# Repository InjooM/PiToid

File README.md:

# PiToid

## Intro
Small beginner's electronics project with Raspberry Pi Zero

This is a small project I started about mid-way through my first semester as a freshman at the University of Georgia. It is a Raspberry Pi in an Altoids Tin that acts as an emulator for video games through Retropie. In order to have a functioning "gameboy" I needed several components:

- A display
- An audio system
- A power management system
- Controls

## Display
For the display, I am using a 1.8" TFT display sold from Adafruit that came with a display driver. It uses SPI to communicate with the Raspberry Pi, so I designed a compact breakout board, referenced from the Adafruit breakout board, that fit my Altoids tin and used an FPC connector.

## Audio
For audio, I configured some of the GPIO pins of the RPi to output audio through PWM, ran it though a low-pass filter, then into an LM4810 audio amp with a 2-gang potentiometer acting as the feedback resistors for the amp. The output is a switching 3.5mm audio jack that runs into 2 8 Ohm speakers. This way I can plug in headphones as well.

## Power
For power management I am using a 3.7V Li-Poly battery sold by Adafruit, and I designed a battery charger and step-up, referenced from the Adafruit PowerBoost 1000 Charger. It also has load-sharing capabilites so when plugged in, the battery will only be charging.

## Controls
For controls I designed a breakout board for the Raspberry Pi and soldered tactile switches onto it, which are connected to the GPIO pins. The Pi is running Adafruit's Retrogame, which configures some GPIO pins as keyboard inputs.

## Final Words
The purpose of this project was not simply to build a DIY gameboy, although I do find gameboys to be fun. I mainly wanted to do this project because I wanted more hands-on experience designing and manufacturing PCB's, as well as putting my circuit analysis skills to the test. Reverse engineering the schematics from Adafruit and reading the datasheets for all the complicated components was difficult, however I believe it helped greatly in developing my electronics design skills. I plan on using these skills in the future for other applications, such as specific instrumentation design.

Most, if not all, of my boards are designed through EAGLE, and fabricated through OshPark. I ordered all my components from Digi-key or Mouser.

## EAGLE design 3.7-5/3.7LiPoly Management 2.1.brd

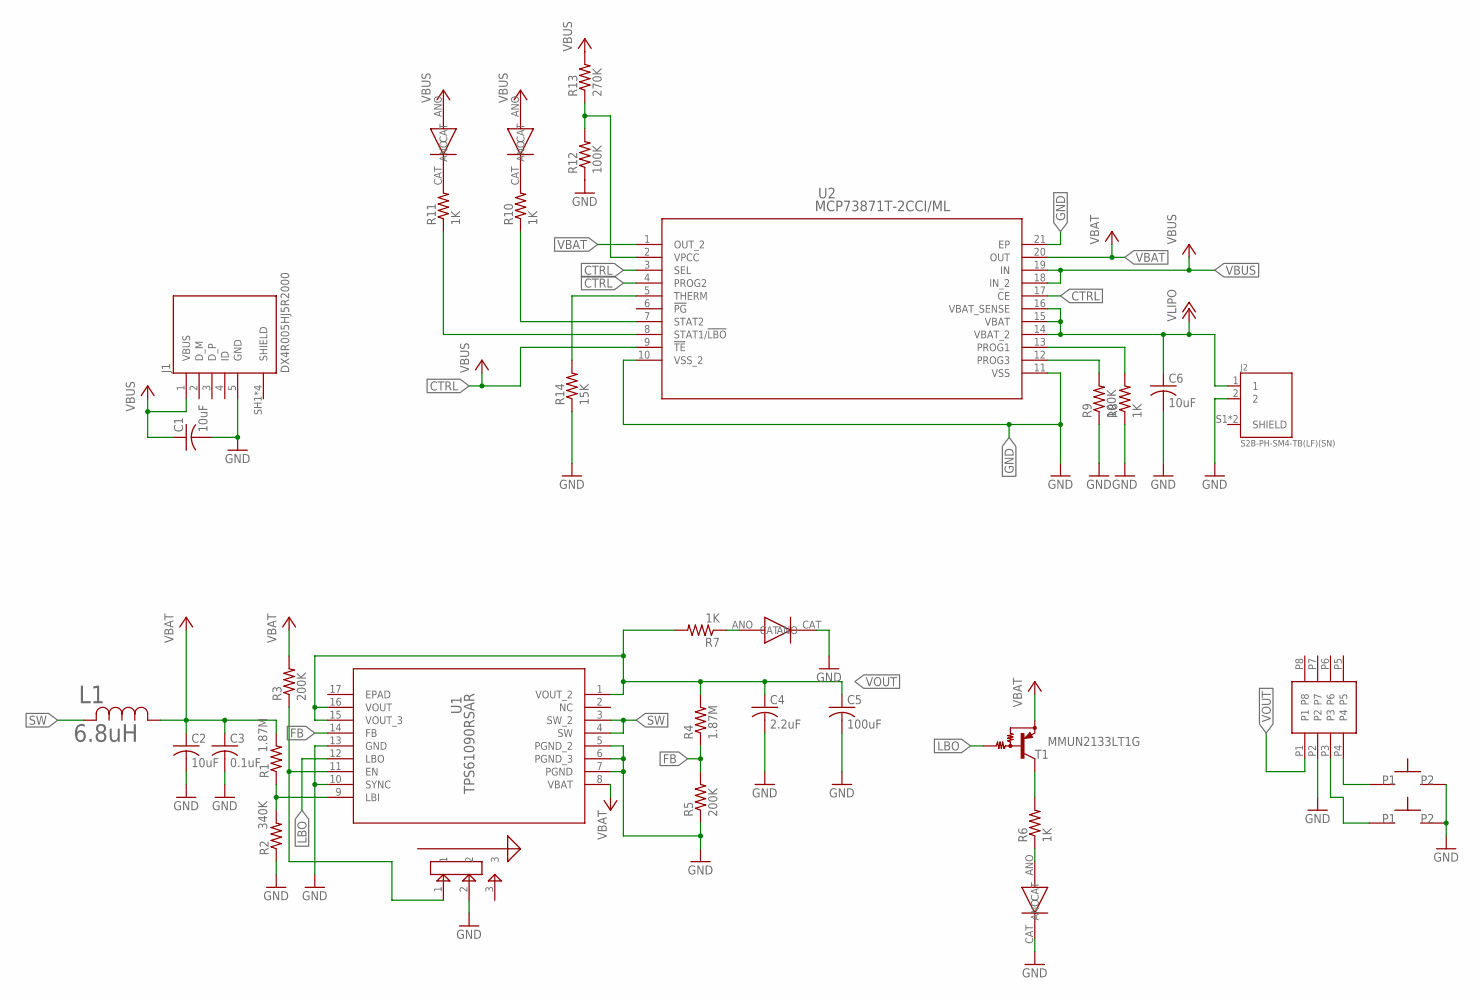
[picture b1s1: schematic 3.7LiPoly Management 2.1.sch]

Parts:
C1, C2, C6: 10uF; C0805
C3: 0.1uF; C0805
C4: 2.2uF; C0805
C5: 100uF; C0805
CHARGE: YELLOW; WP934AD
DONE: GREEN; WP934AD
H1: M22-6340442
J1: DX4R005HJ5R2000; JAE_DX4R005HJ5R2000
J2: S2B-PH-SM4-TB(LF)(SN); JST_S2B-PH-SM4-TB(LF)(SN)
L1: 6.8uH; IND_5028
LBO: RED; WP934AD
POWERON: BLUE; WP934EW
R1, R4: 1.87M; R0805
R2: 340K; R0805
R3, R5: 200K; R0805
R6, R7, R8, R10, R11: 1K; R0805
R9, R12: 100K; R0805
R13: 270K; R0805
R14: 15K; R0805
T1: MMUN2133LT1G; SC59-BEC
U1: TPS61090RSAR; RSA16_2P7X2P7
U2: MCP73871T-2CCI/ML; QFN20_4X4MC
U$1, U$3: SPST_TACTILE_SWITCHRIGHTANGLEBENT; SPST_TACTILESWITCH_TL3360CF185Q_BENTFRAME
U$2: JS102011SAQN

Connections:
+3V3: CHARGE.ANO, DONE.ANO, R13.2
CTRL: U2.3 (SEL), U2.4 (PROG2), U2.9 (!TE), U2.17 (CE)
FB: R4.1, R5.2, U1.14 (FB)
GND: C1.2, C2.2, C3.2, C4.2, C5.2, C6.2, H1.P2, J1.5 (GND), J2.2, LBO.CAT, POWERON.CAT, R2.1, R5.1, R8.1, R9.1, R12.1, R14.1, U1.5 (PGND_2), U1.6 (PGND_3), U1.7 (PGND), U1.10 (SYNC), U1.13 (GND), U2.10 (VSS_2), U2.11 (VSS), U2.21 (EP), U$1.P$2, U$2.2, U$3.P$2
LBO: T1.B, U1.12 (LBO)
unnamed: R1.1, R2.2, U1.9 (LBI)
unnamed: R3.1, U1.11 (EN), U$2.1
unnamed: CHARGE.CAT, R11.2
unnamed: R8.2, U2.13 (PROG1)
unnamed: R6.2, T1.C
unnamed: LBO.ANO, R6.1
unnamed: POWERON.ANO, R7.1
unnamed: R9.2, U2.12 (PROG3)
unnamed: DONE.CAT, R10.2
unnamed: H1.P4, U$3.P$1
unnamed: R11.1, U2.8 (STAT1/!LBO)
unnamed: R10.1, U2.7 (STAT2)
unnamed: R14.2, U2.5 (THERM)
unnamed: R12.2, R13.1, U2.2 (VPCC)
unnamed: H1.P3, U$1.P$1
SW: L1.2, U1.3 (SW_2), U1.4 (SW)
VBAT: C2.1, C3.1, L1.1, R1.2, R3.2, T1.E, U1.8 (VBAT), U2.1 (OUT_2), U2.20 (OUT)
VBUS: C1.1, J1.1 (VBUS), U2.18 (IN_2), U2.19 (IN)
VLIPO: C6.1, J2.1, U2.14 (VBAT_2), U2.15 (VBAT), U2.16 (VBAT_SENSE)
VOUT: C4.1, C5.1, H1.P1, R4.2, R7.2, U1.1 (VOUT_2), U1.15 (VOUT_3), U1.16 (VOUT)

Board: 2 copper layers, 34 parts (0 on the bottom side), 25 nets, no tracks yet.

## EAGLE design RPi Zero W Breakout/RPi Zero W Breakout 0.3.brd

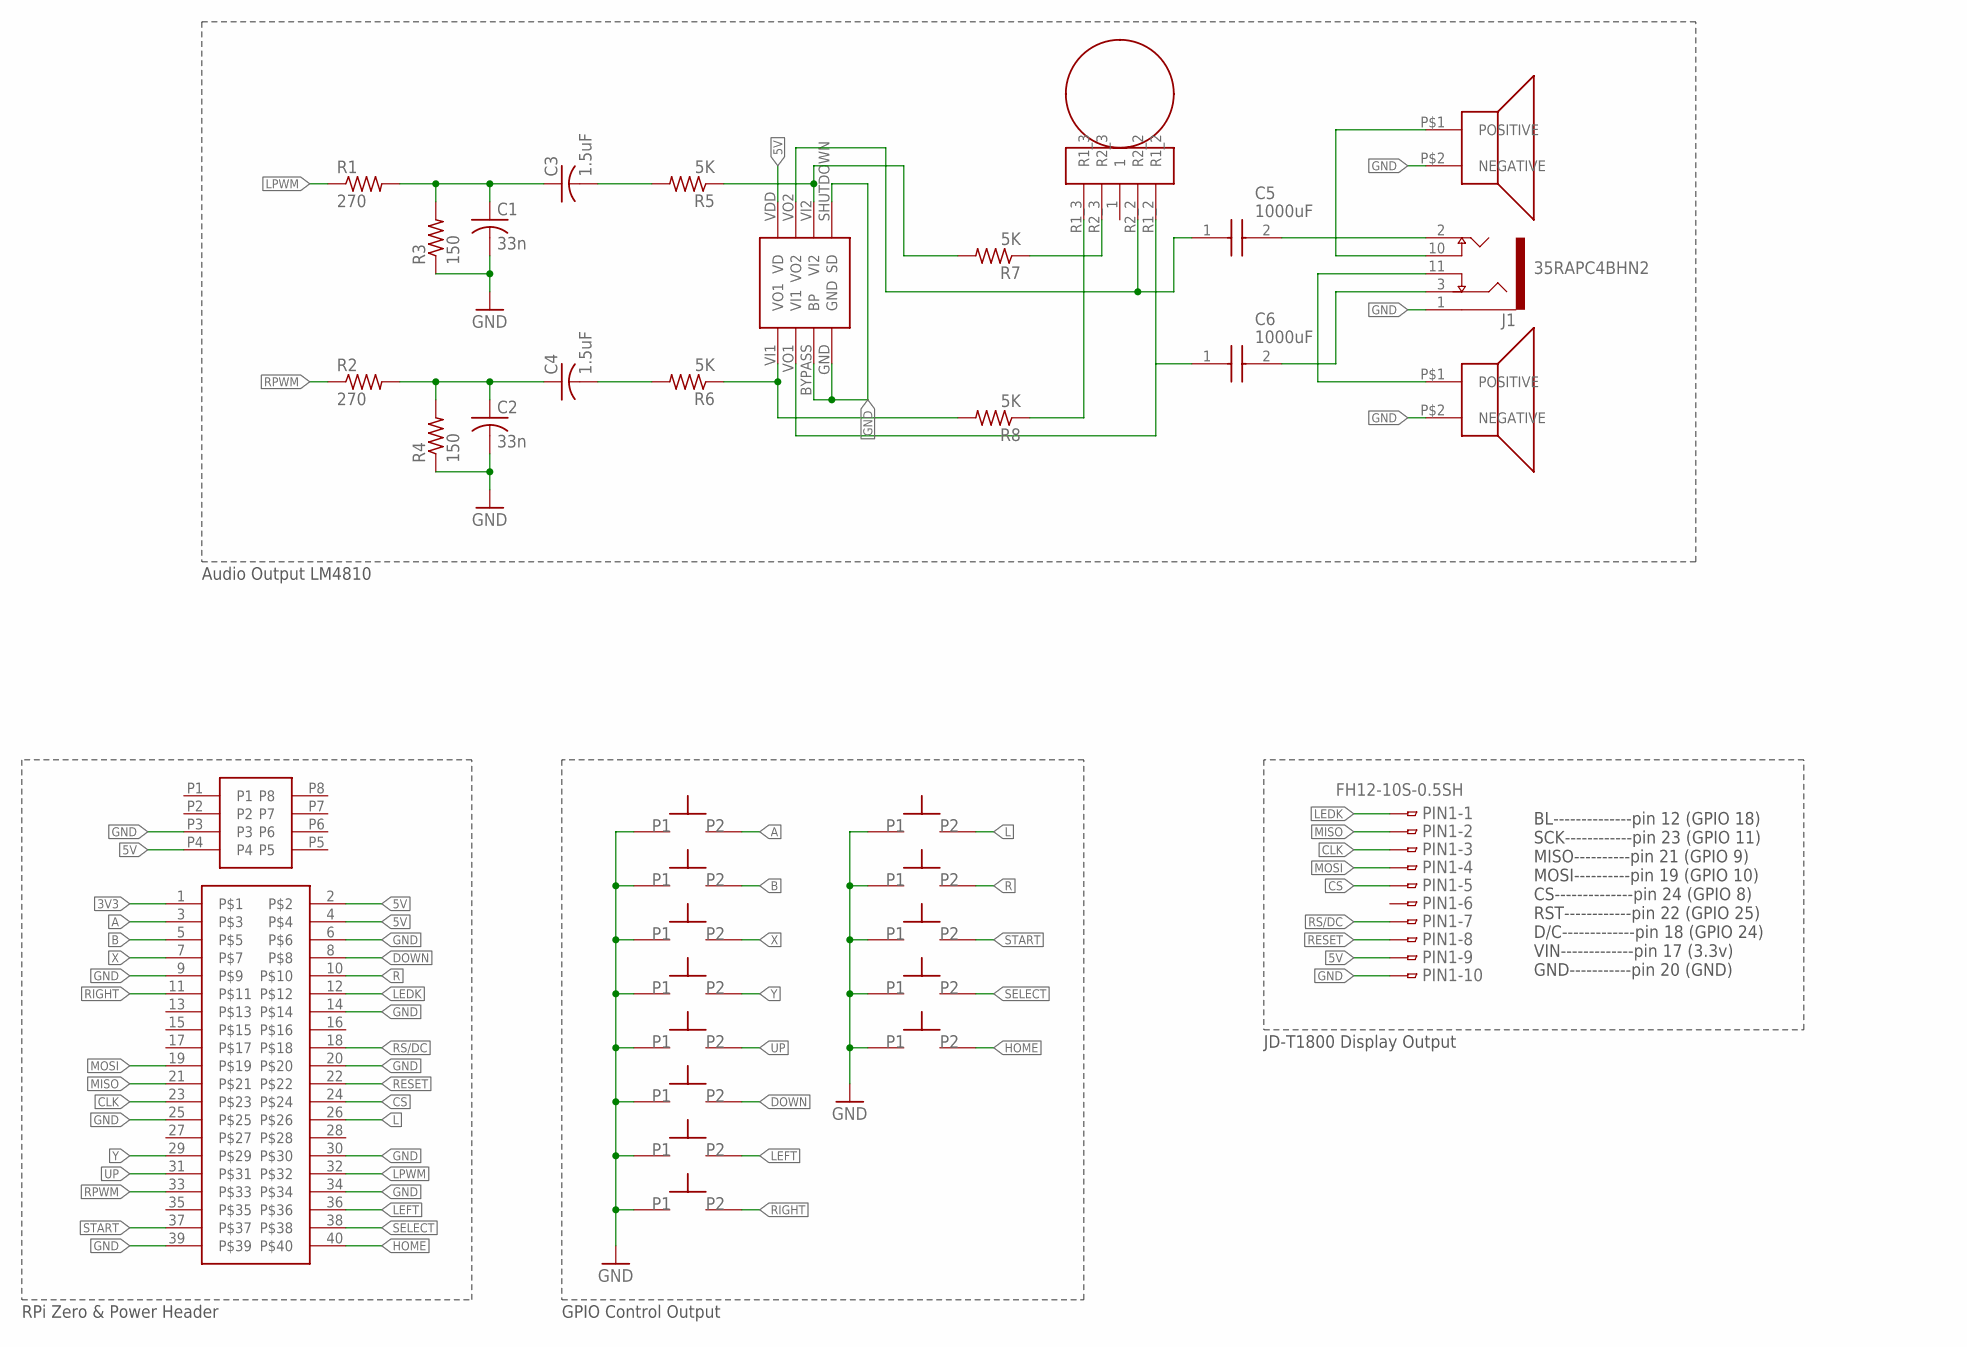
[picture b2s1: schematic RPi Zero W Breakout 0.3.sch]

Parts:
A: SPST_TACTILE_SWITCH; SPST_TACTILESWITCH_TL3301PF160QG
B: SPST_TACTILESWITCH_TL3301PF160QG
C1, C2: 33n; C0805K
C3, C4: 1.5uF; C0805K
C5, C6: 1000uF; UWT(8X10)
DOWN: SPST_TACTILESWITCH_TL3301PF160QG
HOME: SPST_TACTILESWITCH_TL3301PF160QG
J1: 35RAPC4BHN2; SWITCHCRAFT_35RAPC4BHN2
LEFT: SPST_TACTILESWITCH_TL3301PF160QG
LSPK: SP-1208
PIN1: FH12-10S-0.5SH
R1, R2: 270; R0805
R3, R4: 150; R0805
R5, R6, R7, R8: 5K; R0805
RF: RK14J12A0A0K
RIGHT: SPST_TACTILESWITCH_TL3301PF160QG
RSPK: SP-1208
SELECT: SPST_TACTILESWITCH_TL3301PF160QG
START: SPST_TACTILE_SWITCH; SPST_TACTILESWITCH_TL3301PF160QG
U$1: RPI_ZERO
U$2: LM4810MM/NOPBCT-ND; NOPBCT-ND
U$3: M22-6340442
U$4, U$5: SPST_TACTILE_SWITCHRIGHTANGLEBENT; SPST_TACTILESWITCH_TL3360CF185Q_BENTFRAME
UP: SPST_TACTILESWITCH_TL3301PF160QG
X: SPST_TACTILESWITCH_TL3301PF160QG
Y: SPST_TACTILESWITCH_TL3301PF160QG

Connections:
3V3: U$1.1
5V: PIN1.9, U$1.2, U$1.4, U$2.VDD (VD), U$3.P4
A: A.P$3, U$1.3
B: B.P$3, U$1.5
CLK: PIN1.3, U$1.23
CS: PIN1.5, U$1.24
DOWN: DOWN.P$3, U$1.8
GND: A.P$1, B.P$1, C1.2, C2.2, DOWN.P$1, HOME.P$1, J1.1, LEFT.P$1, LSPK.P$2 (NEGATIVE), PIN1.10, R3.1, R4.1, RIGHT.P$1, RSPK.P$2 (NEGATIVE), SELECT.P$1, START.P$1, U$1.6, U$1.9, U$1.14, U$1.20, U$1.25, U$1.30, U$1.34, U$1.39, U$2.BYPASS (BP), U$2.GND, U$2.SHUTDOWN (SD), U$3.P3, U$4.P$1, U$5.P$1, UP.P$1, X.P$1, Y.P$1
HOME: HOME.P$3, U$1.40
L: U$1.26, U$4.P$2
LEDK: PIN1.1, U$1.12
LEFT: LEFT.P$3, U$1.36
LPWM: R1.1, U$1.32
MISO: PIN1.2, U$1.21
MOSI: PIN1.4, U$1.19
unnamed: C1.1, C3.1, R1.2, R3.2
unnamed: C2.1, C4.1, R2.2, R4.2
unnamed: C3.2, R5.2
unnamed: R7.1, RF.R2_3
unnamed: C4.2, R6.2
unnamed: R8.1, RF.R1_3
unnamed: C6.1 (+), RF.R1_2, U$2.VO1 (VI1)
unnamed: C5.1 (+), RF.R2_2, U$2.VO2
unnamed: C5.2 (-), J1.2
unnamed: C6.2 (-), J1.3
unnamed: J1.10, LSPK.P$1 (POSITIVE)
unnamed: J1.11, RSPK.P$1 (POSITIVE)
unnamed: R5.1, R7.2, U$2.VI2
unnamed: R6.1, R8.2, U$2.VI1 (VO1)
R: U$1.10, U$5.P$2
RESET: PIN1.8, U$1.22
RIGHT: RIGHT.P$3, U$1.11
RPWM: R2.1, U$1.33
RS/DC: PIN1.7, U$1.18
SELECT: SELECT.P$3, U$1.38
START: START.P$3, U$1.37
UP: U$1.31, UP.P$3
X: U$1.7, X.P$3
Y: U$1.29, Y.P$3

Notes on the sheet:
BL--------------pin 12 (GPIO 18) SCK------------pin 23 (GPIO 11) MISO----------pin 21 (GPIO 9) MOSI----------pin 19 (GPIO 10) CS--------------pin 24 (GPIO 8) RST------------pin 22 (GPIO 25) D/C-------------pin 18 (GPIO 24) VIN-------------pin 17 (3.3v) GND-----------pin 20 (GND)
RPi Zero & Power Header
GPIO Control Output
JD-T1800 Display Output
Audio Output LM4810

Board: 2 copper layers, 35 parts (4 on the bottom side), 38 nets, no tracks yet.

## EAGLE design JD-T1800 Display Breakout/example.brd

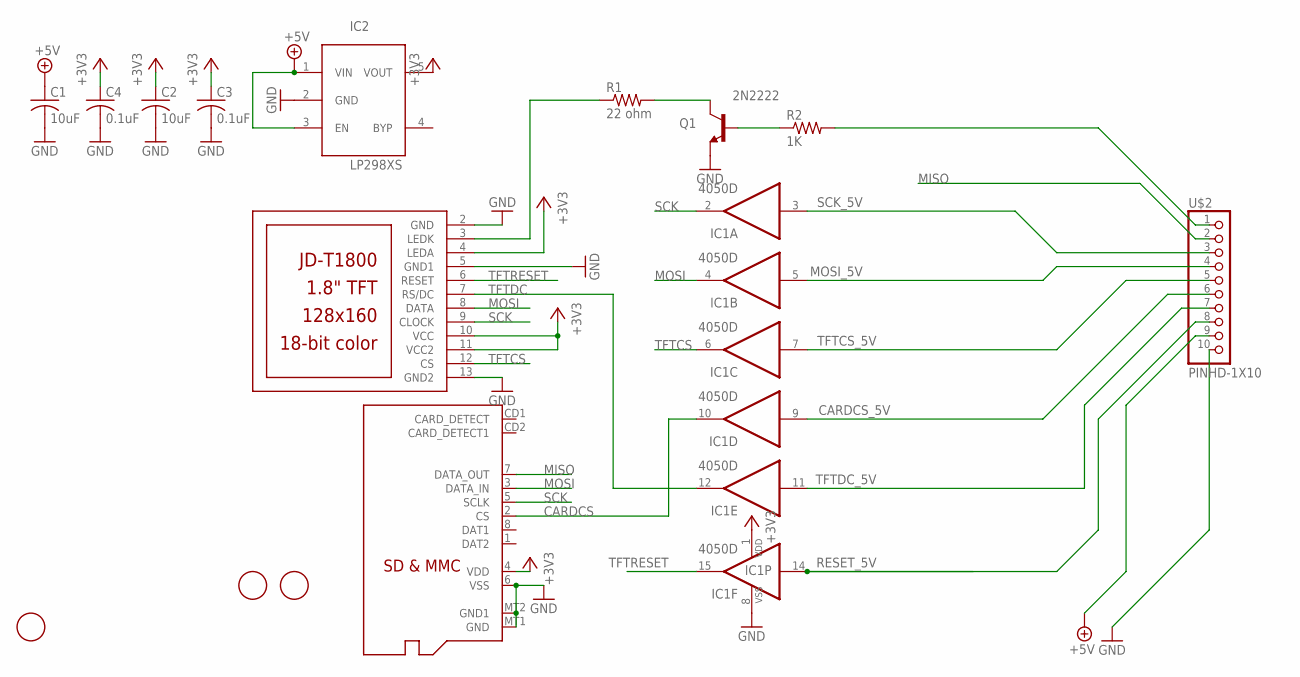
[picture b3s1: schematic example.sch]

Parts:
C1, C2: 10uF; C0805K
C3, C4: 0.1uF; C0805K
IC1: 4050D; SO16
IC2: LP298XS; SOT23-5L
Q1: 2N2222; SOT23-BEC
Q2: MICROSD
R1: 22 ohm; R0805
R2: 1K; R0805
U$1: JD-T1800
U$2: PINHD-1X10; 1X10-BIG
U$3, U$4, U$5: FIDUCIAL; FIDUCIAL_1MM

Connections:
+3V3: C2.1, C3.1, C4.1, IC1.1 (VDD), IC2.5 (VOUT), Q2.4 (VDD), U$1.4 (LEDA), U$1.10 (VCC), U$1.11 (VCC2)
+5V: C1.1, IC2.1 (VIN), IC2.3 (EN), U$2.9
CARDCS: IC1.10 (O), Q2.2 (CS)
CARDCS_5V: IC1.9 (I), U$2.6
GND: C1.2, C2.2, C3.2, C4.2, IC1.8 (VSS), IC2.2 (GND), Q1.E, Q2.6 (VSS), Q2.MT1 (GND), Q2.MT2 (GND1), U$1.2 (GND), U$1.5 (GND1), U$1.13 (GND2), U$2.10
MISO: Q2.7 (DATA_OUT), U$2.2
MOSI: IC1.4 (O), Q2.3 (DATA_IN), U$1.8 (DATA)
MOSI_5V: IC1.5 (I), U$2.4
unnamed: Q1.B, R2.1
unnamed: R1.1, U$1.3 (LEDK)
unnamed: Q1.C, R1.2
unnamed: R2.2, U$2.1
RESET_5V: IC1.14 (I), U$2.8
SCK: IC1.2 (O), Q2.5 (SCLK), U$1.9 (CLOCK)
SCK_5V: IC1.3 (I), U$2.3
TFTCS: IC1.6 (O), U$1.12 (CS)
TFTCS_5V: IC1.7 (I), U$2.5
TFTDC: IC1.12 (O), U$1.7 (RS/DC)
TFTDC_5V: IC1.11 (I), U$2.7
TFTRESET: IC1.15 (O), U$1.6 (RESET)

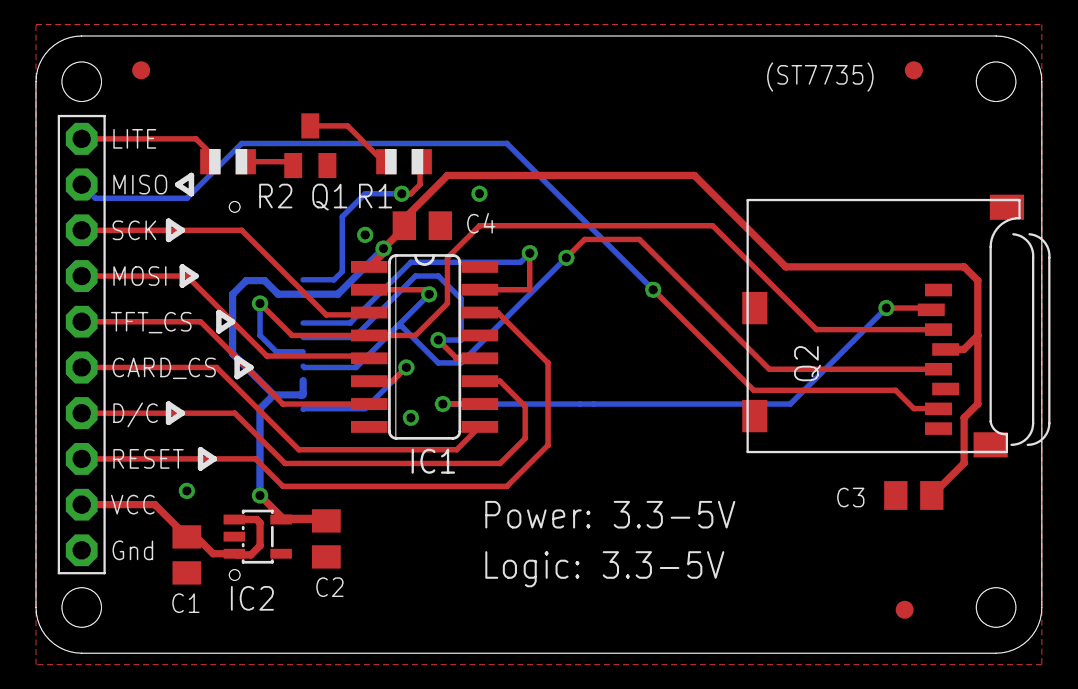
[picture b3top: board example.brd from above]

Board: 2 copper layers, 55.9 x 34.3 mm, 15 parts (1 on the bottom side), 20 nets.

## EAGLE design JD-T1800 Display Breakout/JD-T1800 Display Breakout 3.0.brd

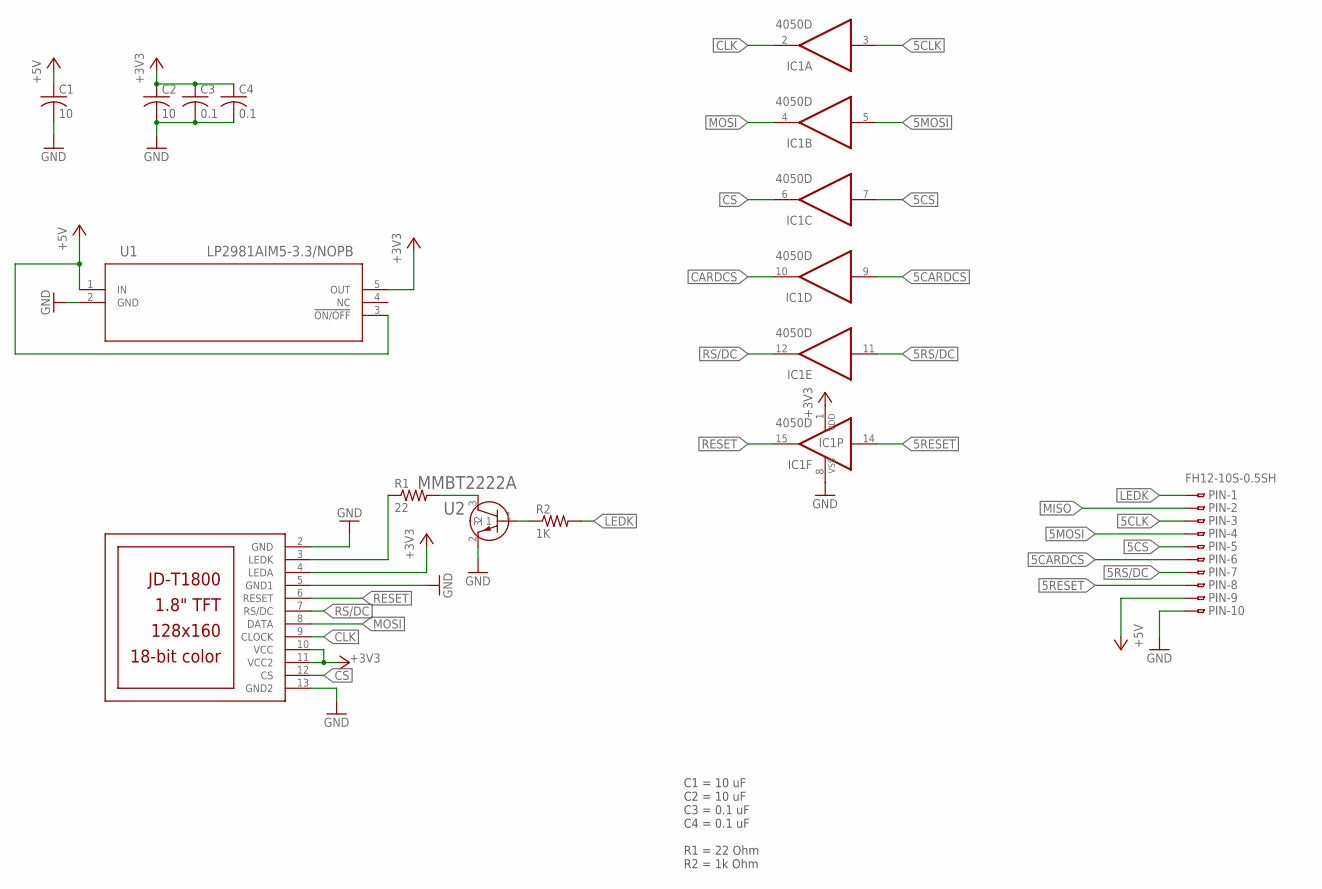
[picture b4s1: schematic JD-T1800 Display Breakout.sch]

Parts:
C1, C2: 10; C0805
C3, C4: 0.1; C0805
IC1: 4050D; SO16
PIN: FH12-10S-0.5SH
R1: 22; R0805
R2: 1K; R0805
U1: LP2981AIM5-3.3/NOPB; MF05A
U2: MMBT2222A; SOT23
U$1: JD-T1800

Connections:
5CARDCS: IC1.9 (I), PIN.6
5CLK: IC1.3 (I), PIN.3
5CS: IC1.7 (I), PIN.5
5MOSI: IC1.5 (I), PIN.4
5RESET: IC1.14 (I), PIN.8
5RS/DC: IC1.11 (I), PIN.7
+3V3: C2.1, C3.1, C4.1, IC1.1 (VDD), U1.5 (OUT), U$1.4 (LEDA), U$1.10 (VCC), U$1.11 (VCC2)
+5V: C1.1, PIN.9, U1.1 (IN), U1.3 (!ON/OFF)
CARDCS: IC1.10 (O)
CLK: IC1.2 (O), U$1.9 (CLOCK)
CS: IC1.6 (O), U$1.12 (CS)
GND: C1.2, C2.2, C3.2, C4.2, IC1.8 (VSS), PIN.10, U1.2 (GND), U2.2, U$1.2 (GND), U$1.5 (GND1), U$1.13 (GND2)
LEDK: PIN.1, R2.2
MISO: PIN.2
MOSI: IC1.4 (O), U$1.8 (DATA)
unnamed: R1.1, U$1.3 (LEDK)
unnamed: R1.2, U2.3
unnamed: R2.1, U2.1
RESET: IC1.15 (O), U$1.6 (RESET)
RS/DC: IC1.12 (O), U$1.7 (RS/DC)

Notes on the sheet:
C1 = 10 uF C2 = 10 uF C3 = 0.1 uF C4 = 0.1 uF R1 = 22 Ohm R2 = 1k Ohm

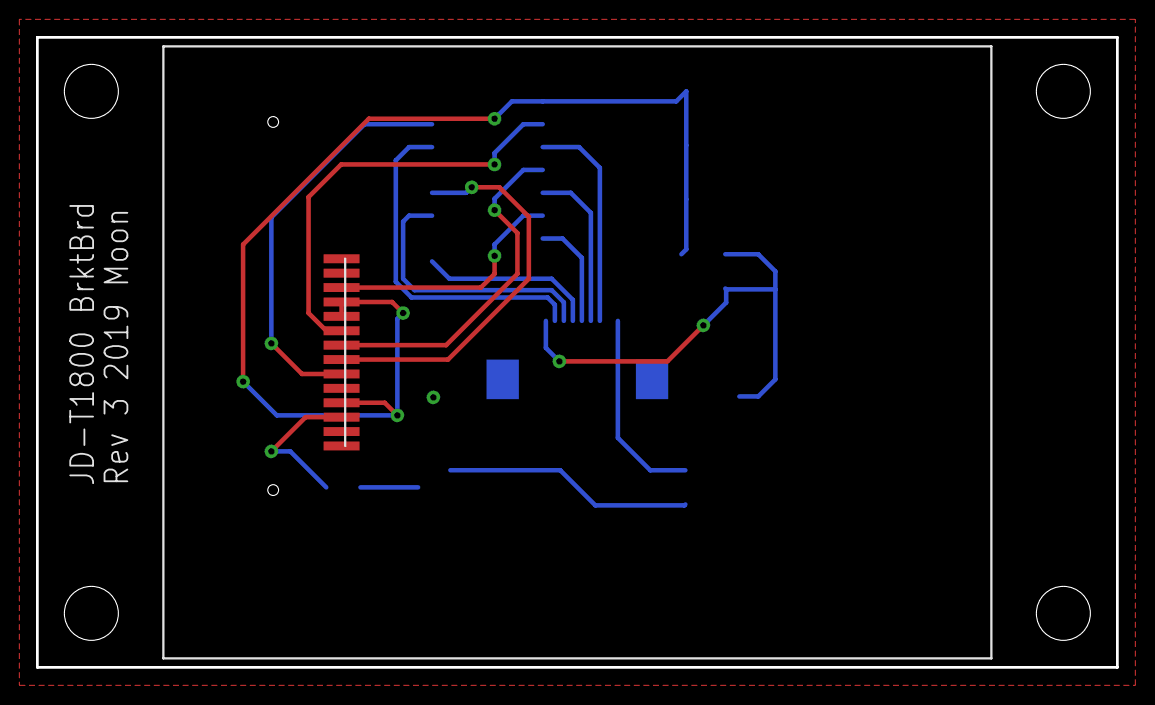
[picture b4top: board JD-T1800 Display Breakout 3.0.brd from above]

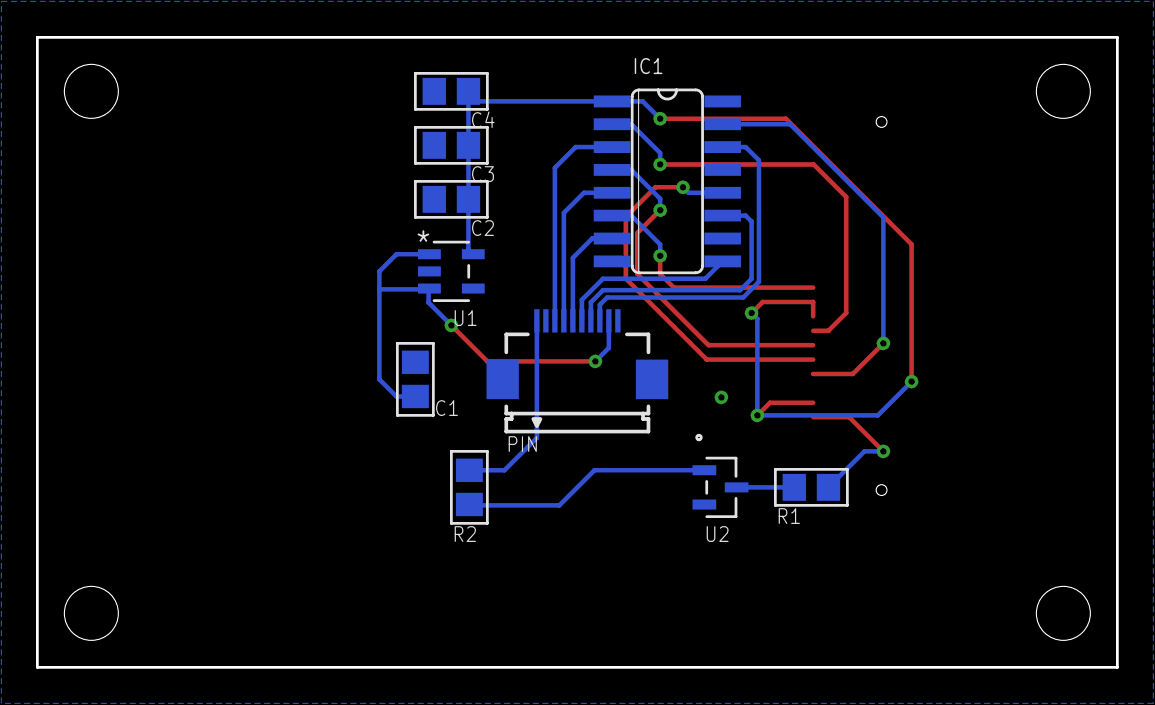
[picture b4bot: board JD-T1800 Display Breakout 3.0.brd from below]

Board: 2 copper layers, 60.0 x 35.0 mm, 11 parts (10 on the bottom side), 18 nets.

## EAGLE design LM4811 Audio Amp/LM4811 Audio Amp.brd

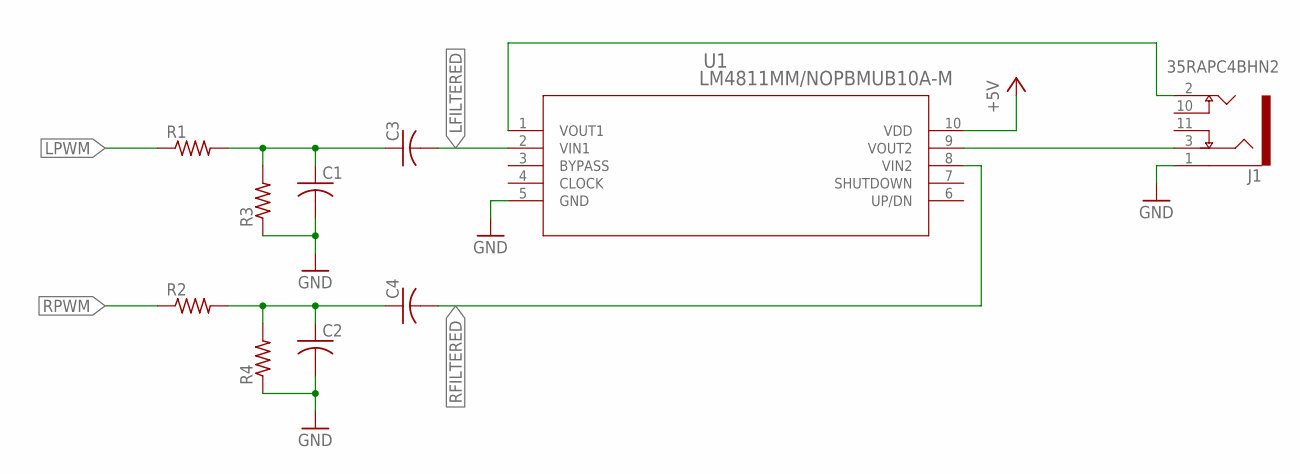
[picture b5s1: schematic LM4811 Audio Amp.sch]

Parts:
C1, C2, C3, C4: C-USC0805K; C0805K
J1: 35RAPC4BHN2; SWITCHCRAFT_35RAPC4BHN2
R1, R2, R3, R4: R-US_R0805; R0805
U1: LM4811MM/NOPBMUB10A-M; MUB10A-M

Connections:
+5V: U1.10 (VDD)
GND: C1.2, C2.2, J1.1, R3.1, R4.1, U1.5 (GND)
LFILTERED: C3.2, U1.2 (VIN1)
LPWM: R1.1
unnamed: C1.1, C3.1, R1.2, R3.2
unnamed: C2.1, C4.1, R2.2, R4.2
unnamed: J1.2, U1.1 (VOUT1)
unnamed: J1.3, U1.9 (VOUT2)
RFILTERED: C4.2, U1.8 (VIN2)
RPWM: R2.1

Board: 2 copper layers, 10 parts (0 on the bottom side), 7 nets, no tracks yet.

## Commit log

2018-11-22 Update ReadMe 11-21-18
2018-11-22 ReadMe Update 11-21-18
    Formatting
2019-02-14 Add files via upload
    Uploading boards/schem that I've been working on. Some of these are not the 1st revisions.
2019-02-28 Update
    Getting more familiar with Git and updating cleanly
2019-02-28 Reorganizing
    Reorganizing folders
2019-02-28 Rename
    Renamed files to correct versions
2019-03-01 RPi Zero W Breakout Rev 0.3
    Cleaned up schematic symbols and finalized schematic.
2019-03-04 Update
    Finished RPi Zero Breakout Schem and board layout. Need to route. Moved LiPoly Management's power headers so it aligned with RPi Breakout's. Still need to find perfect tactile buttons for RPi Breakou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
2019-03-04 RPi Zero Complete
    Finished routing RPi Zero, ERC and DRC came out okay.
2019-03-04 Update
    minor layer changes for text
2019-03-04 More layer changes
    Just moving text between layers for silkscreen. Just realized that RPi 0.3 is saved as 1.0, but oh well.
2019-03-05 Update
    Moved shoulder buttons to LiPoly Management and extended LiPoly Management's dimensions. After looking at the boards in Fusion 360, I decided it would be better to have the shoulder buttons lower, ra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
2019-03-05 Minor update
    Repositioned buttons
2019-03-05 Update
    Added more mounting holes and made all holes M2.5
